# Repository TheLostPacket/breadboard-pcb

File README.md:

This is a fork of https://github.com/tebl/breadboard the design has been changed to my specification and simplified to allow easier manafacturer

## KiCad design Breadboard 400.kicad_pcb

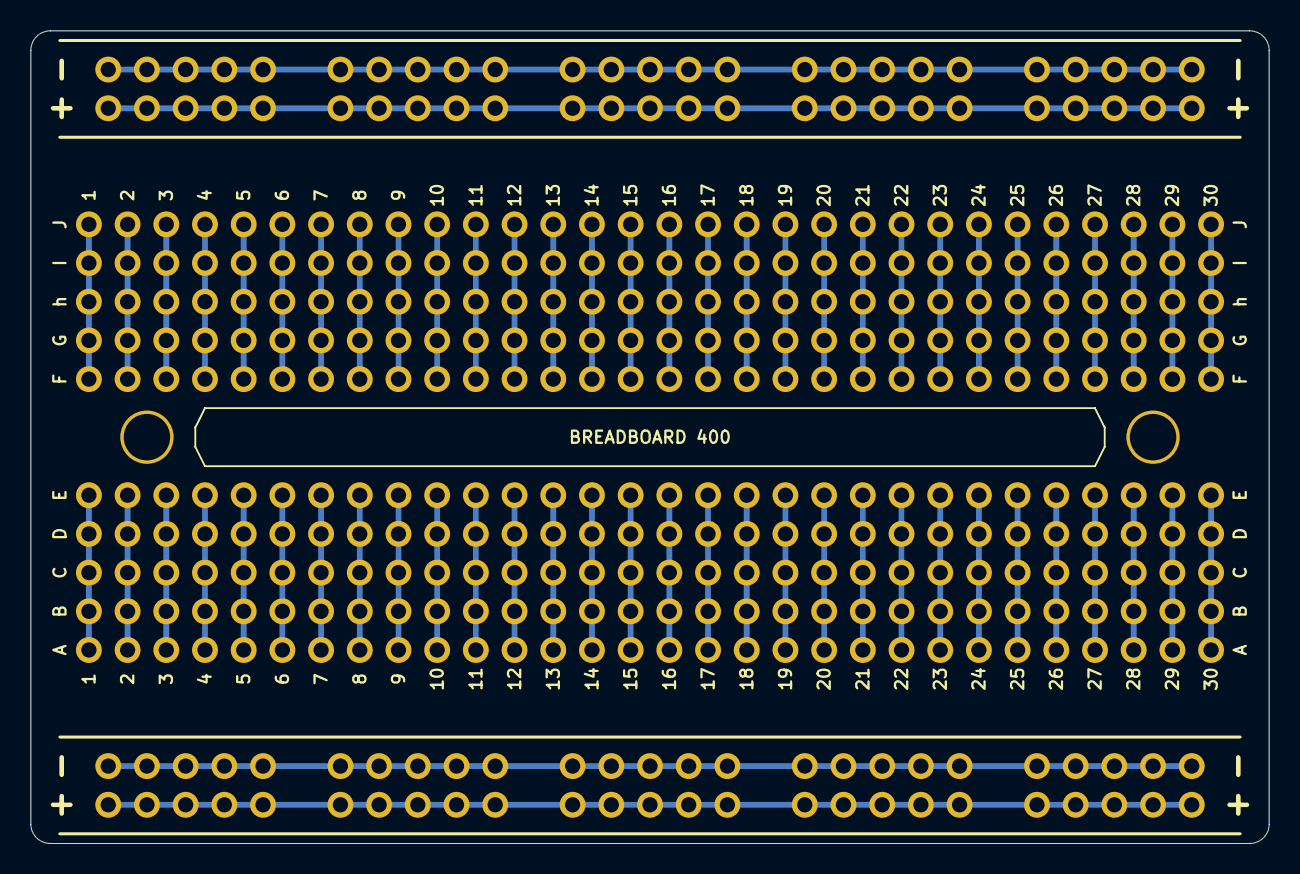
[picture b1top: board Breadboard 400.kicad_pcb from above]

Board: 2 copper layers, 81.3 x 53.3 mm, 42 parts (0 on the bottom side), 4 nets.

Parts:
A1, A2, A3, A4, A5, A11, A12, A13, A14, A15: PWR; power
A6, A7, A8, A9, A10, A16, A17, A18, A19, A20, A21, A22, A23, A24, A25, A26, A27, A28, A29, A30, A31, A32, A33, A34, A35, A36, A37, A38, A39, A40: BB; section
H1, H2: MountingHole; M3

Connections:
/GND1: A1.2, A2.2, A3.2, A4.2, A5.2
/GND2: A11.2, A12.2, A13.2, A14.2, A15.2
/VCC1: A1.1, A2.1, A3.1, A4.1, A5.1
/VCC2: A11.1, A12.1, A13.1, A14.1, A15.1

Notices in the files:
Breadboard 400.kicad_pcb:
Licensed under
CERN OHL v1.2
